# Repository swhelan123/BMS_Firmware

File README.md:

# BMS Firmware

STM32F303VC-based Battery Management System — firmware, desktop tool, and complete
pre-hardware validation stack.

> **No hardware has been flashed yet.**  
> All workflows below run entirely in simulation unless noted otherwise.  
> See [First-Flash Warning](#first-flash-warning) before connecting real hardware.

---

## Quick Start

```bash
# 1. Clone and enter the repo
git clone <repo-url>
cd BMS_Firmware

# 2. Install dev environment (creates .venv, checks toolchain)
./scripts/setup_dev_env.sh

# 3. Run the full validation suite (no hardware needed)
./scripts/validate_all.sh

# 4. Run the interactive CLI demo against the fake target
./scripts/demo_local.sh

# 5. Launch the desktop GUI with the fake target
./scripts/run_gui.sh --fake --mode healthy
```

---

## Project Structure

```
BMS_Firmware/
├── firmware/               STM32F303VC application firmware (C11)
│   ├── src/
│   │   ├── bms/            Core BMS logic (config, faults, balance, measurements)
│   │   ├── drivers/        LTC6812 isoSPI driver, ISL28022 I2C power monitor
│   │   └── board/          STM32 BSP (SPI, UART, outputs, clock, flash)
│   ├── include/            Public headers
│   └── cmake/              Toolchain file + CMakeLists.txt
├── bootloader/             STM32 bootloader (sector 0, 32 KB)
│   ├── src/                bl_validate.c, bl_jump.c, bl_update.c
│   └── include/
├── tool/                   Python desktop tool (CLI + GUI)
│   ├── src/
│   │   ├── core/           AppState, TargetModel, PollingLoop, ConnectionManager
│   │   ├── protocol/       Framing, CRC, BmsProtocolClient, packet_defs
│   │   ├── config/         BmsConfig schema, validator
│   │   ├── update/         Package builder/parser, BootloaderUpdater, ST-Link wrapper
│   │   ├── fake_target/    Full BMS simulator — 12 modes, TCP or in-process
│   │   ├── cli/            bmsctl.py — thin CLI over the shared backend
│   │   ├── gui/            PyQt6 desktop app (9 tabs)
│   │   └── connection/     DeviceState, DeviceMode, CapabilitiesState
│   ├── tests/              ~330 pytest tests (no hardware required)
│   └── requirements.txt    pyserial, PyYAML, pytest, PyQt6
├── tests/                  C unit tests (Unity framework)
│   ├── unit/               test_pec15.c, test_balance.c, test_openwire.c, …
│   ├── mock_bsp/           Mock SPI/UART/outputs/clock/flash
│   └── vendor/unity/
├── scripts/
│   ├── setup_dev_env.sh        One-command dev environment setup
│   ├── validate_all.sh         One-command full validation
│   ├── demo_local.sh           Full stack demo (fake target, CLI, optional GUI)
│   ├── run_gui.sh              Launch GUI (with optional fake target)
│   ├── bmsctl.sh               CLI wrapper (activates .venv)
│   ├── build_firmware.sh       STM32 firmware build
│   ├── flash_stlink.sh         Dry-run and real flash via ST-Link (--execute required)
│   ├── first_flash_dry_run.sh  Pre-hardware readiness check (no flash)
│   └── package_release.sh      Create dist/ release bundle
├── protocol/               Protocol specification documents
├── docs/                   Design documents (hardware contract, safety model, etc.)
└── build_firmware/         CMake build output (gitignored)
```

---

## Setup

```bash
./scripts/setup_dev_env.sh
```

Creates `.venv`, installs `tool/requirements.txt`, and checks for:

| Tool | Required for | Install |
|------|-------------|---------|
| Python 3.11+ | Everything | https://python.org |
| arm-none-eabi-gcc | Firmware build | brew install --cask gcc-arm-embedded |
| cmake | Firmware build | brew install cmake |
| ninja | Firmware build | brew install ninja |
| clang | C unit tests | included with Xcode CLT |
| STM32_Programmer_CLI | ST-Link flash (optional) | https://st.com/stm32cubeprog |
| PyQt6 | Desktop GUI | pip install PyQt6 |

---

## Validate Everything

```bash
./scripts/validate_all.sh                   # full suite with firmware build
./scripts/validate_all.sh --no-firmware     # skip STM32 build
```

Runs: tool detection → pytest suite → fake-target self-test → config round-trip →
package + update simulation → firmware build.

Expected output: `33 passed  0 failed  0-5 skipped` (skipped = optional tools absent).

---

## Run Tests

### Python tests (~330)
```bash
python3 -m pytest tool/tests/ -q
```

### C unit tests (181 across 14 suites)
```bash
bash build_tests/run_tests.sh
```

Covers: PEC-15, measurements decode, protocol CRC, config validate/masks, outputs,
flash layout, bootloader validate, bootloader protocol state machine, faults, cell
balancing, open-wire detection.

---

## Build Firmware

```bash
export PATH="/Applications/ArmGNUToolchain/15.2.rel1/arm-none-eabi/bin:$PATH"
./scripts/build_firmware.sh           # release build
./scripts/build_firmware.sh debug     # debug build
```

Artifacts in `build_firmware/`:

| File | Description |
|------|-------------|
| `firmware.bin` | Raw binary, flash at 0x08008000 |
| `firmware.hex` | Intel HEX, flash at 0x08008000 |
| `bms_firmware.elf` | ELF with debug symbols |
| `firmware.map` | Linker map (section sizes, symbols) |

---

## CLI Tool

```bash
./scripts/bmsctl.sh --help
```

Activates `.venv` automatically.

```bash
# Start fake target in one terminal
./scripts/bmsctl.sh fake-target run --mode healthy

# In another terminal
./scripts/bmsctl.sh connect
./scripts/bmsctl.sh values
./scripts/bmsctl.sh cells -v
./scripts/bmsctl.sh temps
./scripts/bmsctl.sh faults --json
./scripts/bmsctl.sh diagnostics
./scripts/bmsctl.sh openwire run

# Config
./scripts/bmsctl.sh config export-default --out default.bin
./scripts/bmsctl.sh config validate default.bin
./scripts/bmsctl.sh config export-json default.bin
./scripts/bmsctl.sh config apply-ram default.bin

# Package + update
./scripts/bmsctl.sh package build firmware.bin fw.pkg --version 1.0.0
./scripts/bmsctl.sh package validate fw.pkg
./scripts/bmsctl.sh update simulate fw.pkg    # test protocol update flow
./scripts/bmsctl.sh update dry-run fw.pkg     # print steps without running
```

---

## Desktop GUI

```bash
./scripts/run_gui.sh --fake                          # healthy mode
./scripts/run_gui.sh --fake --mode openwire_detected # test open-wire tab
./scripts/run_gui.sh --fake --mode cell_uv           # test undervoltage fault
./scripts/run_gui.sh --fake --mode bootloader        # test update simulation
```

**Tabs:**
| Tab | Description |
|-----|-------------|
| Connection | TCP (fake target) or serial port; device capabilities |
| Bring-Up | Diagnostics counters, GPIO snapshot, chain probes, one-shot measurements, open-wire, balance disable-all |
| Dashboard | Pack voltage, current, state, uptime, polling controls |
| Cells | 75-cell voltage table; measure-once; invalid cells highlighted |
| Temperatures | 75-sensor table; measure-once; invalid sensors highlighted |
| Faults | Active + latched bitmaps; named fault list; clear latched |
| Config | Read/load/save/validate/apply-RAM; export default |
| Firmware Flash | Package inspect/validate; protocol update simulation; ST-Link gate |
| Logs | Event + packet logs |

---

## Fake Target

Simulates the full BMS protocol stack. Available modes:

| Mode | Description |
|------|-------------|
| `healthy` | 75 cells at 3700 mV, 25°C, no faults |
| `safe_invalid` | Zero cells, all temps INVALID, no faults |
| `cell_uv` | cell[0]=2400 mV, FAULT_CELL_UV active |
| `cell_ov` | cell[0]=4300 mV, FAULT_CELL_OV active |
| `temp_invalid` | All temps INVALID, FAULT_TEMP_READ_INVALID |
| `vpack_invalid` | FAULT_VPACK_INVALID active |
| `isospi_fault` | FAULT_ISOSPI_CELL active |
| `config_error` | FAULT_CONFIG_INVALID active |
| `precharge_fault` | FAULT_PRECHARGE_TIMEOUT active |
| `bootloader` | Responds as FIRMWARE_TYPE_BOOTLOADER |
| `openwire_detected` | Open-wire scan returns cell[0] flagged |
| `openwire_pec_fail` | Open-wire scan returns PEC error status |

Self-test (all modes):
```bash
./scripts/bmsctl.sh fake-target self-test
```

---

## Full Demo

```bash
./scripts/demo_local.sh             # CLI demo: connect, measure, config, package
./scripts/demo_local.sh --gui       # same + launch GUI at end
```

---

## First-Flash Preparation

> **No hardware has been flashed yet.** The firmware has been validated in simulation only.
> Read the documents listed below before connecting any hardware.

```bash
# 1. Validate the full software stack (no hardware required)
./scripts/validate_all.sh --no-firmware

# 2. Build firmware (requires arm-none-eabi-gcc)
export PATH="/Applications/ArmGNUToolchain/15.2.rel1/arm-none-eabi/bin:$PATH"
./scripts/build_firmware.sh

# 3. Run the first-flash readiness check (dry-run only, no real flash)
./scripts/first_flash_dry_run.sh

# 4. Read before connecting hardware (in order):
#    docs/bench_safety_checklist.md
#    docs/first_flash_guide.md
#    docs/uart_smoke_test.md
#    docs/01_hardware_contract.md  (especially §16 hardware validation questions)
```

Flash command (after safety checklist is complete):

```bash
# Dry-run first — prints exact command, does not flash
./scripts/flash_stlink.sh --app build_firmware/firmware.bin

# Real flash — requires --execute
./scripts/flash_stlink.sh --app build_firmware/firmware.bin --execute
```

First CLI session after flash:

```bash
PORT=/dev/tty.usbserial-XXXX   # find with: ls /dev/tty.usbserial-*
./scripts/bmsctl.sh connect    --serial $PORT
./scripts/bmsctl.sh diagnostics --serial $PORT
./scripts/bmsctl.sh diag gpio   --serial $PORT
./scripts/bmsctl.sh diag outputs --serial $PORT
```

### First-Flash Documents

| Document | Read when |
|----------|-----------|
| `docs/bench_safety_checklist.md` | Before applying power to the board |
| `docs/first_flash_guide.md` | Full first-flash procedure with pass/fail checklist |
| `docs/uart_smoke_test.md` | Diagnosing serial / protocol connection issues |
| `docs/01_hardware_contract.md` | Pin table, isoSPI topology, open hardware questions |
| `docs/02_safety_model.md` | Permission output semantics and safety invariants |

---

## Package Release

```bash
./scripts/package_release.sh
```

Creates `dist/bms-v{VERSION}/` containing firmware artifacts, Python tool source,
scripts (including `flash_stlink.sh` and `first_flash_dry_run.sh`), docs (including all
first-flash guides), and auto-generated release notes and manifest. No `.venv`,
`__pycache__`, or build caches are included.

---

## What Is Simulated (no hardware needed)

- All 12 fake target modes including fault injection, openwire, bootloader
- Full BMS protocol (framing, CRC, all packet types)
- Firmware update flow: enter-bootloader → begin → chunks → finalize
- Config read/write/validate/apply-RAM
- Cell balancing logic (C unit tests with mock SPI)
- Open-wire detection algorithm (C unit tests with mock SPI)
- Fault bit mapping and masking (C unit tests)
- Package build/parse/validate (Python tests)
- GUI polling, state display, all page interactions
- ST-Link dry-run (generates command without executing)

---

## What Remains Hardware-Dependent

| Item | Status |
|------|--------|
| UART/serial communication with real target | Not tested |
| isoSPI chain bring-up (LTC6812) | Not tested |
| ISL28022 I2C power monitor | Not tested |
| ADC calibration (Vpack, Vbat, Ibat) | Not tested |
| GPIO output states (MasterOK, Discharge, Charge, ChargerSafety) | Not tested |
| Precharge timing | Not tested |
| CAN bus | Not tested |
| Power-latch / power-button | Not tested |
| Thermal runaway under real cell conditions | Not tested |
| Actual flash/erase timing on STM32 | Not tested |
| Bootloader PEC verification on real SPI | Not tested |

---

## First-Flash Warning

> **Read this before connecting any hardware.**

1. The firmware has **not been tested on hardware**. Flash into a bench setup
   with no high-voltage pack attached.
2. `board_outputs_init_safe()` deasserts all permission outputs on startup.
   Verify this physically before attaching any contactor or interlock circuit.
3. Review `docs/01_hardware_contract.md` (pin table) and
   `docs/02_safety_model.md` (safety boundary) before first power-on.
4. Do not enable cell balancing until voltage measurements have been verified
   against a known-good reference.
5. Do not enable charging/discharging permission outputs until all fault
   thresholds have been reviewed and the config has been validated.
6. Use `./scripts/bmsctl.sh diagnostics` on first connect to verify PEC/I2C
   error counters are zero before trusting any measurement.
7. Run `./scripts/bmsctl.sh openwire run` before enabling balance to confirm
   all cell connections are intact.

---

## Design Documents

| Document | Content |
|----------|---------|
| `docs/00_system_purpose.md` | Purpose, safety boundary, what BMS does/doesn't do |
| `docs/01_hardware_contract.md` | Pin table, signal directions, notes |
| `docs/02_safety_model.md` | Fault taxonomy, permission outputs, invariants |
| `docs/03_firmware_architecture.md` | Module structure, state machine, polling loop |
| `docs/04_protocol_contract.md` | Packet format, all packet IDs, error codes |
| `docs/05_config_schema.md` | All config fields, types, ranges, defaults |
| `docs/06_flash_and_bootloader.md` | Flash layout, bootloader update flow |
| `docs/07_desktop_tool_design.md` | Tool architecture, GUI tabs, fake target strategy |
| `docs/08_validation_plan.md` | Test strategy, hardware bring-up checklist |

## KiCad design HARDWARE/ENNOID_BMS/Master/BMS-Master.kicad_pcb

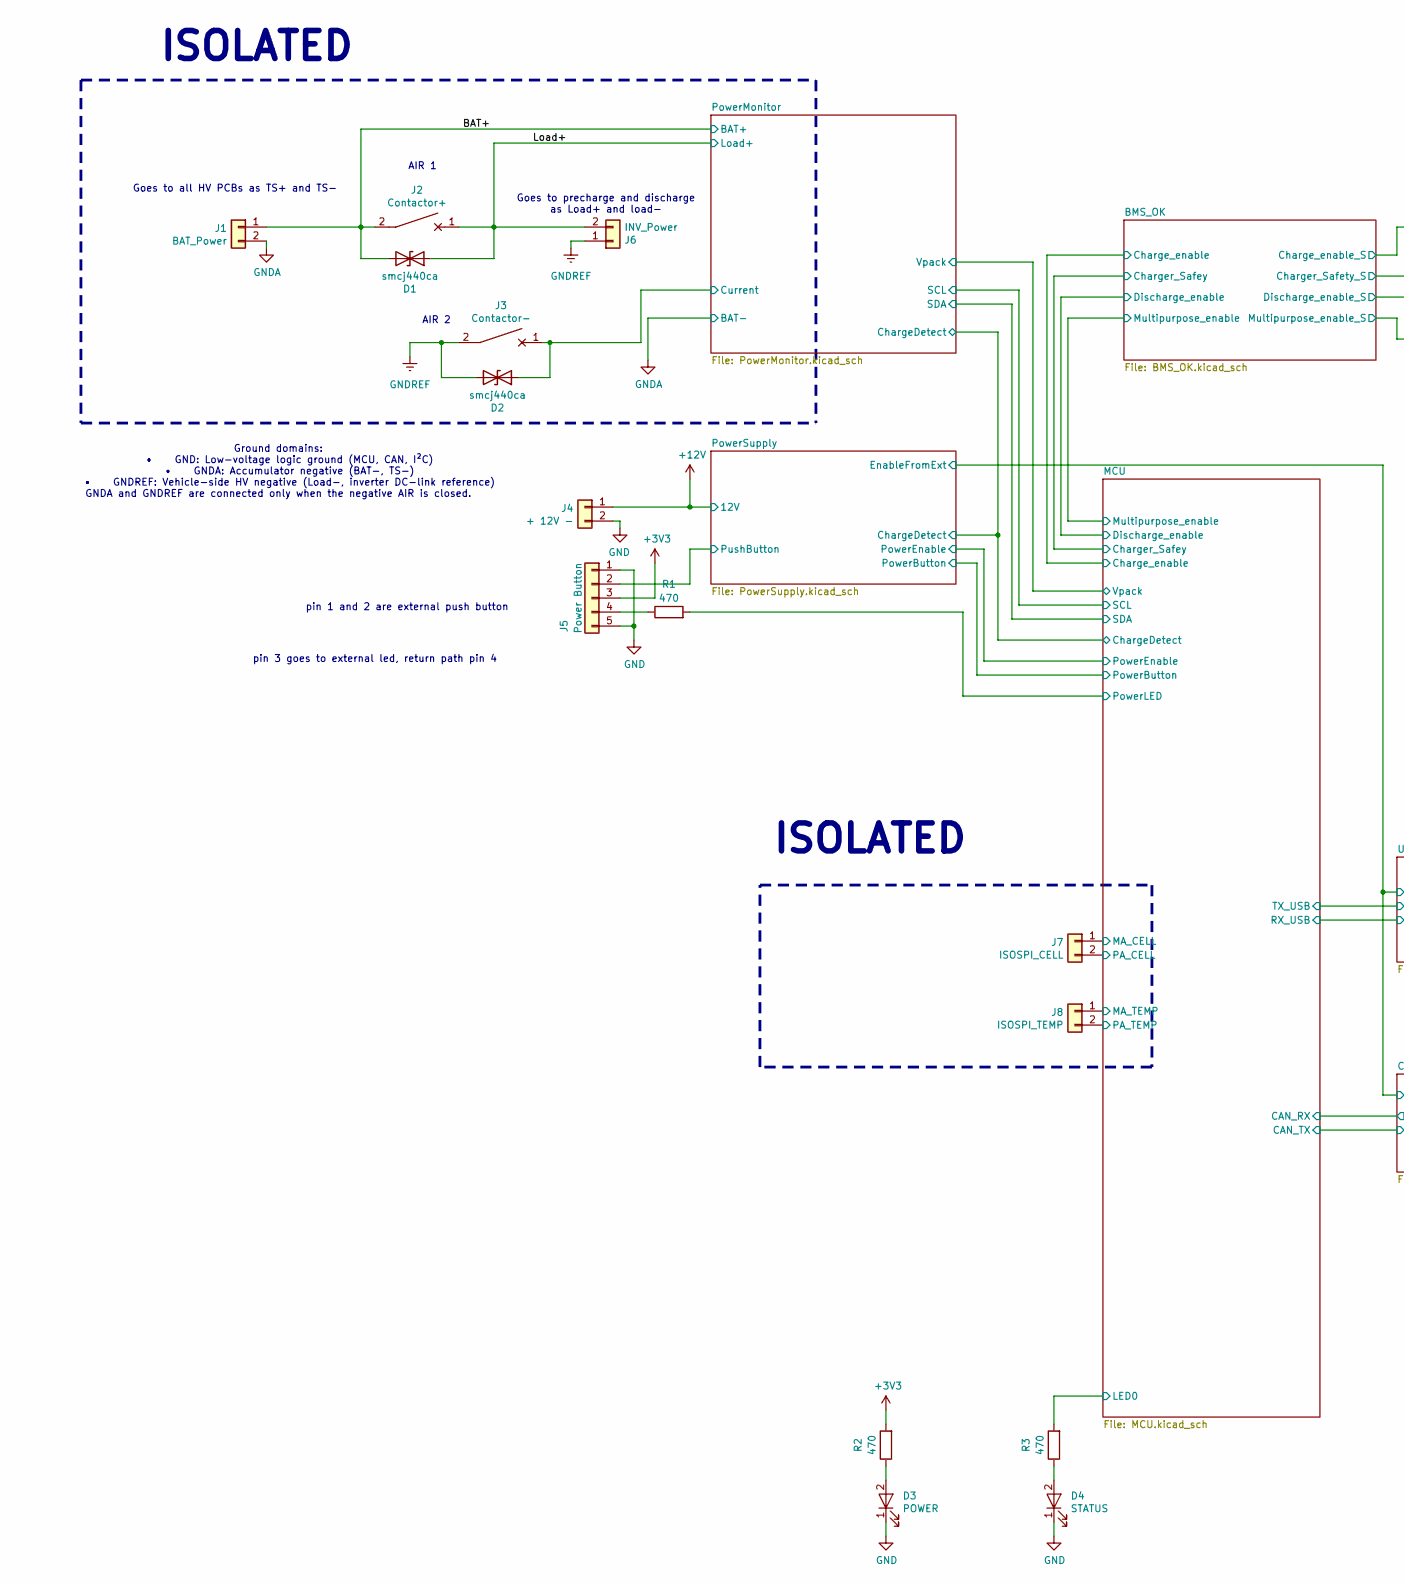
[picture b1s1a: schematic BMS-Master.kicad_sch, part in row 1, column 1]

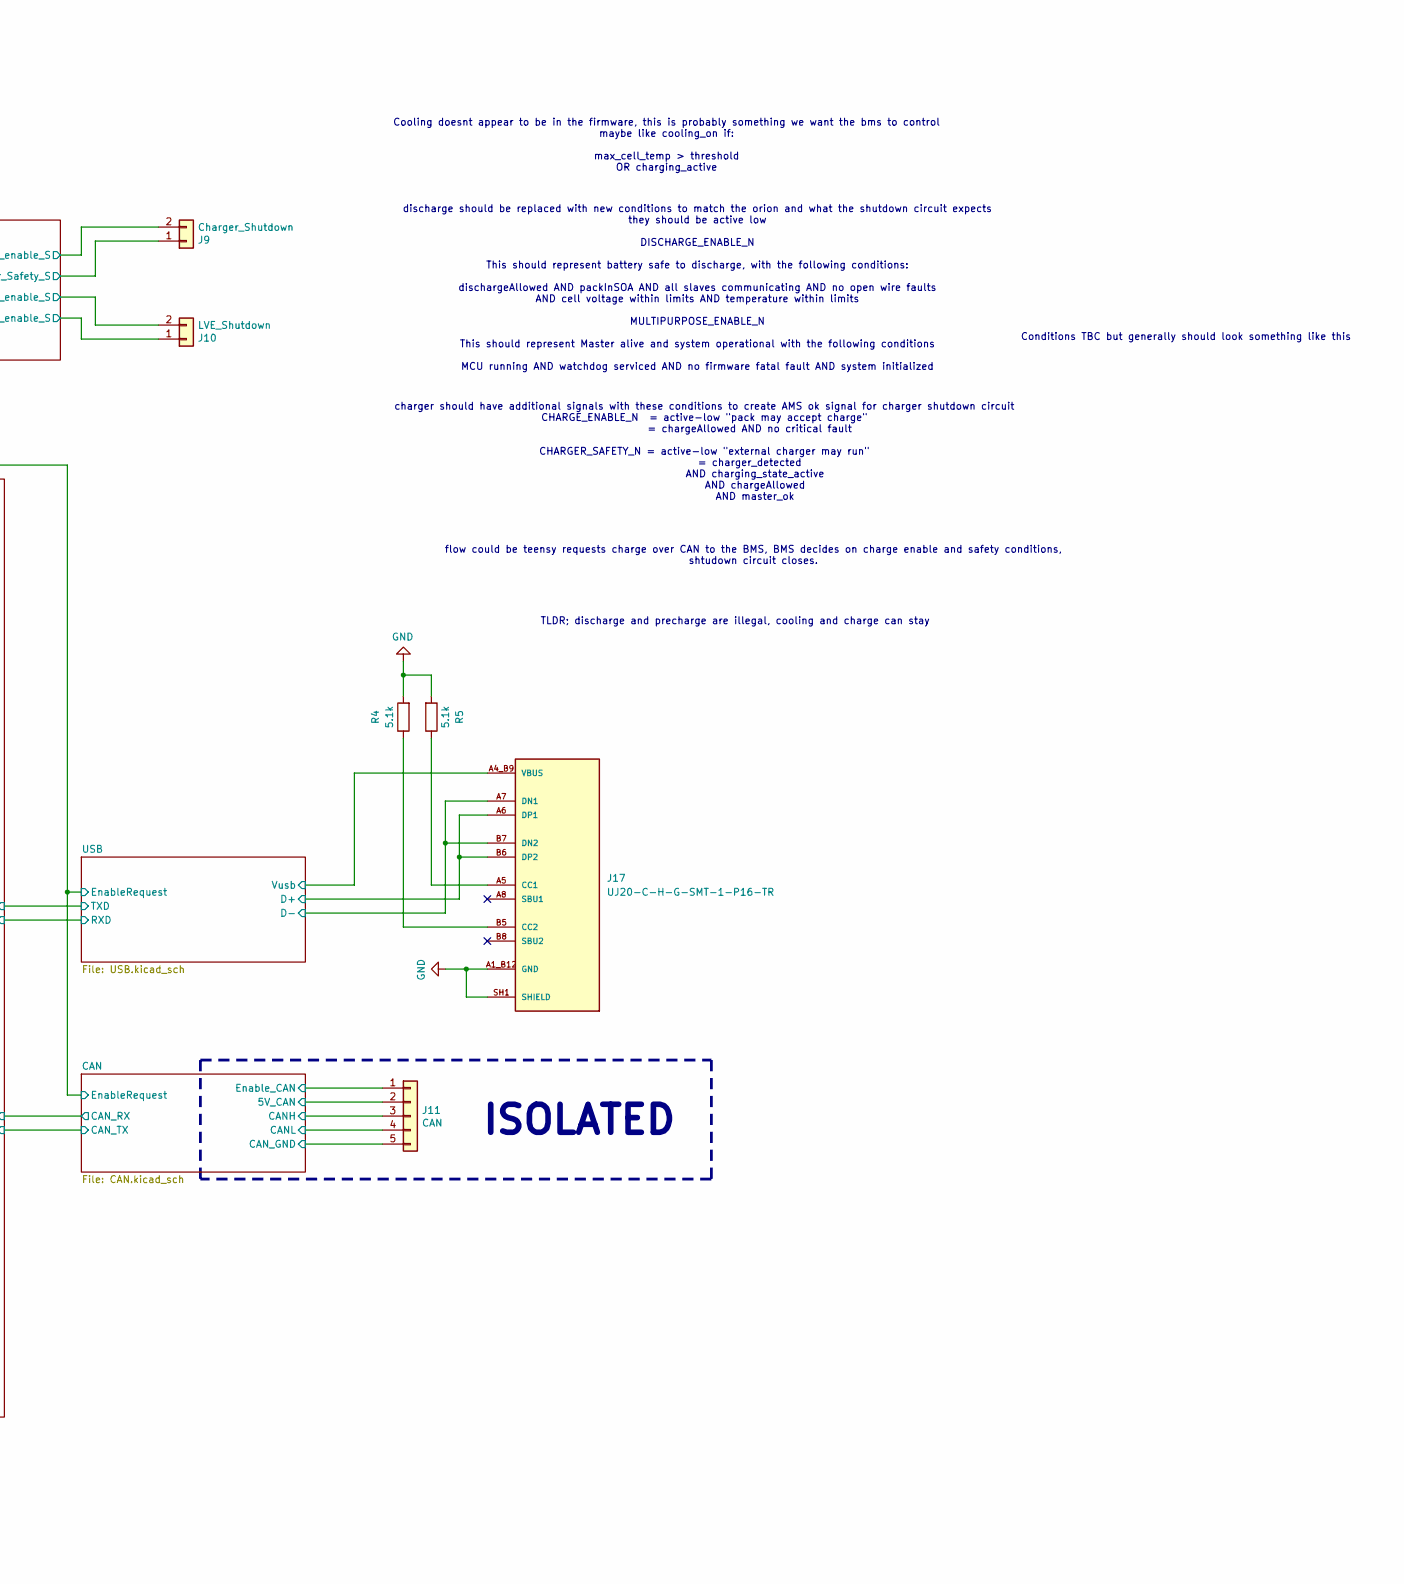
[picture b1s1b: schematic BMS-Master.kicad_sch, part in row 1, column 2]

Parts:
D1, D2: smcj440ca; D_SMC; MPN smcj440ca
D3: POWER; LED_0603_1608Metric; MPN SML-D12P8WT86C
D4: STATUS; LED_0603_1608Metric; MPN SML-D12P8WT86C
J1: BAT_Power; Phoenix_1x2_1729128; MPN 1729128
J2: Contactor+; EVC500; MPN N/A
J3: Contactor-; EVC500; MPN N/A
J4: + 12V -; JST_XH_B2B-XH-A_1x02_P2.50mm_Vertical; MPN B2B-XH-A
J5: Power Button; JST_XH_B5B-XH-A_1x05_P2.50mm_Vertical; MPN B5B-XH-A
J6: INV_Power; Phoenix_1x2_1729128; MPN 1729128
J7: ISOSPI_CELL; JST_XH_B2B-XH-A_1x02_P2.50mm_Vertical; MPN B2B-XH-A
J8: ISOSPI_TEMP; JST_XH_B2B-XH-A_1x02_P2.50mm_Vertical; MPN B2B-XH-A
J9: Charger_Shutdown; JST_XH_B2B-XH-A_1x02_P2.50mm_Vertical; MPN B2B-XH-A
J10: LVE_Shutdown; JST_XH_B2B-XH-A_1x02_P2.50mm_Vertical; MPN B2B-XH-A
J11: CAN; JST_XH_B5B-XH-A_1x05_P2.50mm_Vertical; MPN B5B-XH-A
J17: UJ20-C-H-G-SMT-1-P16-TR; SAMESKY_UJ20-C-H-G-SMT-1-P16-TR; MPN UJ20-C-H-G-SMT-1-P16-TR
R1, R2, R3: 470; R_0603_1608Metric; MPN RC0603JR-07470RL
R4, R5: 5.1k; R_0603_1608Metric; MPN RC0603JR-075K1L

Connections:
+3V3: J5.3, R2.2; also elsewhere on the board
+12V: J4.1; also elsewhere on the board
/BAT+: D1.2 (A2), J1.1, J2.2; also elsewhere on the board
/BMS_OK/Charge_enable_S: J9.2; also elsewhere on the board
/BMS_OK/Charger_Safety_S: J9.1; also elsewhere on the board
/BMS_OK/Discharge_enable_S: J10.2; also elsewhere on the board
/BMS_OK/Multipurpose_enable_S: J10.1; also elsewhere on the board
/CAN/5V_CAN: J11.2; also elsewhere on the board
/CAN/CANH: J11.3; also elsewhere on the board
/CAN/CANL: J11.4; also elsewhere on the board
/CAN/CAN_GND: J11.5; also elsewhere on the board
/CAN/Enable_CAN: J11.1; also elsewhere on the board
/Load+: D1.1 (A1), J2.1, J6.2; also elsewhere on the board
/MCU/LED0: R3.2; also elsewhere on the board
/MCU/MA_CELL: J7.1; also elsewhere on the board
/MCU/MA_TEMP: J8.1; also elsewhere on the board
/MCU/PA_CELL: J7.2; also elsewhere on the board
/MCU/PA_TEMP: J8.2; also elsewhere on the board
/MCU/PowerLED: R1.2; also elsewhere on the board
/PowerMonitor/Current: D2.1 (A1), J3.1; also elsewhere on the board
/PowerSupply/PushButton: J5.2; also elsewhere on the board
/USB/D+: J17.A6 (DP1), J17.B6 (DP2); also elsewhere on the board
/USB/D-: J17.A7 (DN1), J17.B7 (DN2); also elsewhere on the board
/USB/Vusb: J17.A4_B9 (VBUS), J17.B4_A9 (VBUS); also elsewhere on the board
GND: D3.1 (K), D4.1 (K), J4.2, J5.1, J5.5, J17.A1_B12 (GND), J17.B1_A12 (GND), J17.SH1 (SHIELD), J17.SH2 (SHIELD), J17.SH3 (SHIELD), J17.SH4 (SHIELD), R4.2, R5.2; also elsewhere on the board
GNDA: J1.2; also elsewhere on the board
GNDREF: D2.2 (A2), J3.2, J6.1; also elsewhere on the board
unnamed: D3.2 (A), R2.1
unnamed: D4.2 (A), R3.1
unnamed: J5.4, R1.1
unnamed: J17.A5 (CC1), R5.1
unnamed: J17.B5 (CC2), R4.1

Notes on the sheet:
Ground domains: • GND: Low-voltage logic ground (MCU, CAN, I²C) • GNDA: Accumulator negative (BAT−, TS−) • GNDREF: Vehicle-side HV negative (Load−, inverter DC-link reference) GNDA and GNDREF are connected only when the negative AIR is closed.
Goes to all HV PCBs as TS+ and TS-
flow could be teensy requests charge over CAN to the BMS, BMS decides on charge enable and safety conditions, shtudown circuit closes.
Conditions TBC but generally should look something like this
AIR 1
ISOLATED
pin 3 goes to external led, return path pin 4
charger should have additional signals with these conditions to create AMS ok signal for charger shutdown circuit CHARGE_ENABLE_N = active-low "pack may accept charge" = chargeAllowed AND no critical fault CHARGER_SAFETY_N = active-low "external charger may run" = charger_detected AND charging_stat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
AIR 2
Cooling doesnt appear to be in the firmware, this is probably something we want the bms to control maybe like cooling_on if: max_cell_temp > threshold OR charging_active
discharge should be replaced with new conditions to match the orion and what the shutdown circuit expects they should be active low DISCHARGE_ENABLE_N This should represent battery safe to discharge, with the following conditions: dischargeAllowed AND packInSOA AND all slaves communicating AND no o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
Goes to precharge and discharge as Load+ and load-
pin 1 and 2 are external push button
TLDR; discharge and precharge are illegal, cooling and charge can stay

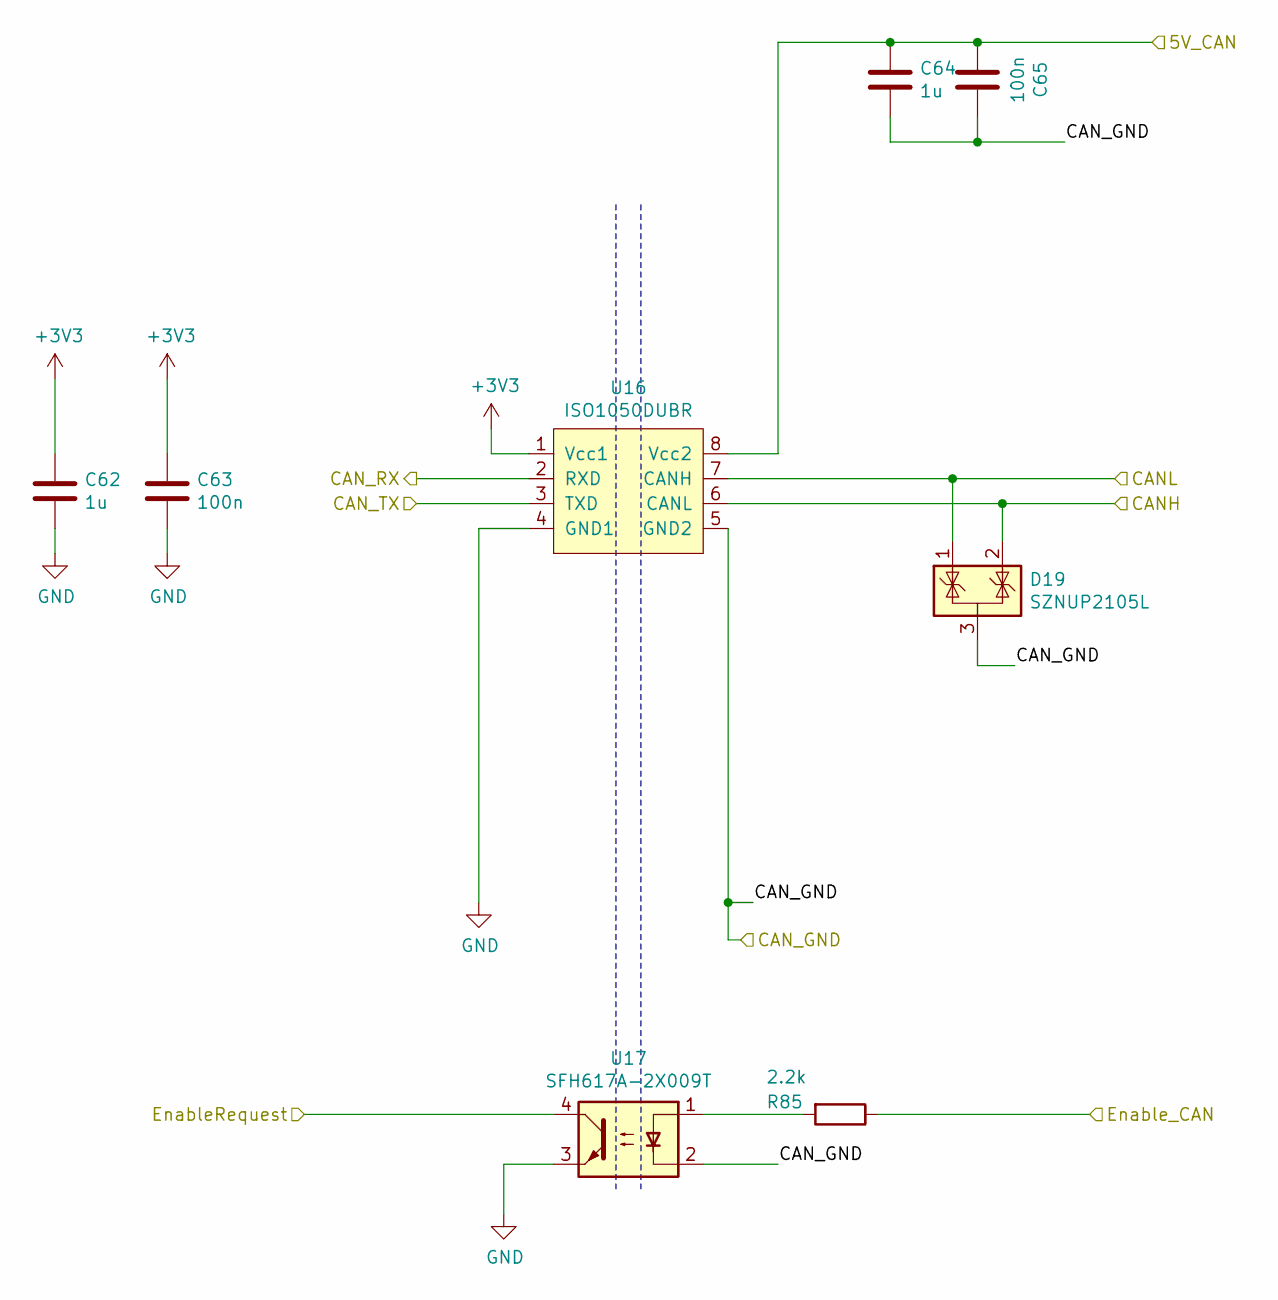
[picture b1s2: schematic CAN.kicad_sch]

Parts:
C62, C64: 1u; C_0603_1608Metric; MPN GRM188R71E105KA12D
C63, C65: 100n; C_0603_1608Metric; MPN GRM188R71E104KA01D
D19: SZNUP2105L; SOT-23; MPN SZNUP2105LT1G
R85: 2.2k; R_0603_1608Metric; MPN RC0603JR-072K2L
U16: ISO1050DUBR; ISO1050; MPN ISO1050DUBR
U17: SFH617A-2X009T; SMDIP-4_W9.53mm_Clearance8mm; MPN SFH617A-2X009T

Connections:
+3V3: C62.1, C63.1, U16.1 (Vcc1); also elsewhere on the board
/CAN/5V_CAN: C64.1, C65.2, U16.8 (Vcc2); also elsewhere on the board
/CAN/CANH: D19.2 (K), U16.6 (CANL); also elsewhere on the board
/CAN/CANL: D19.1 (K), U16.7 (CANH); also elsewhere on the board
/CAN/CAN_GND: C64.2, C65.1, D19.3 (A), U16.5 (GND2), U17.2; also elsewhere on the board
/CAN/CAN_RX: U16.2 (RXD); also elsewhere on the board
/CAN/CAN_TX: U16.3 (TXD); also elsewhere on the board
/CAN/EnableRequest: U17.4; also elsewhere on the board
/CAN/Enable_CAN: R85.1; also elsewhere on the board
GND: C62.2, C63.2, U16.4 (GND1), U17.3; also elsewhere on the board
unnamed: R85.2, U17.1

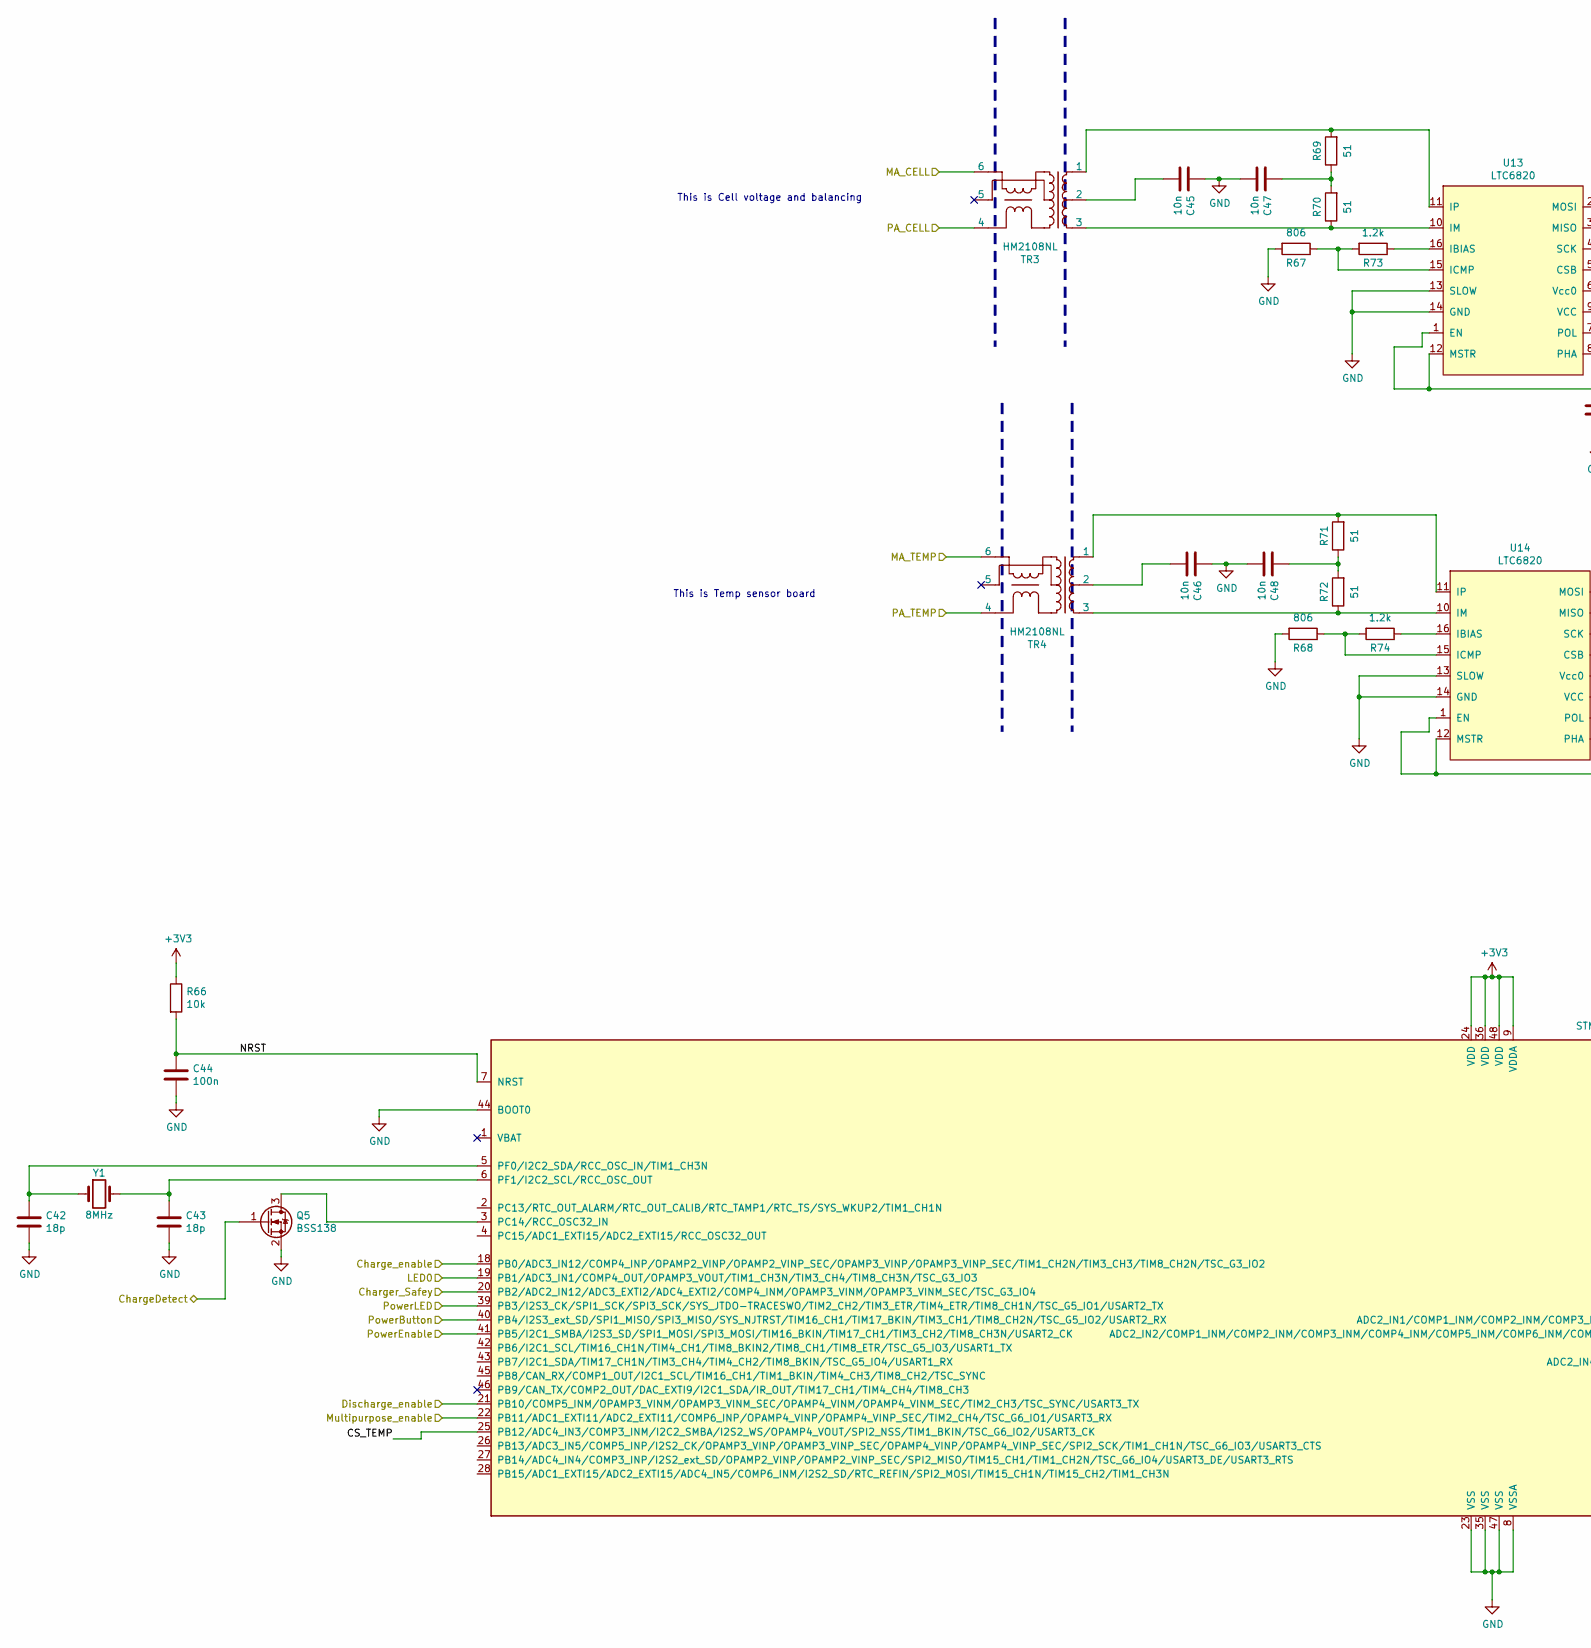
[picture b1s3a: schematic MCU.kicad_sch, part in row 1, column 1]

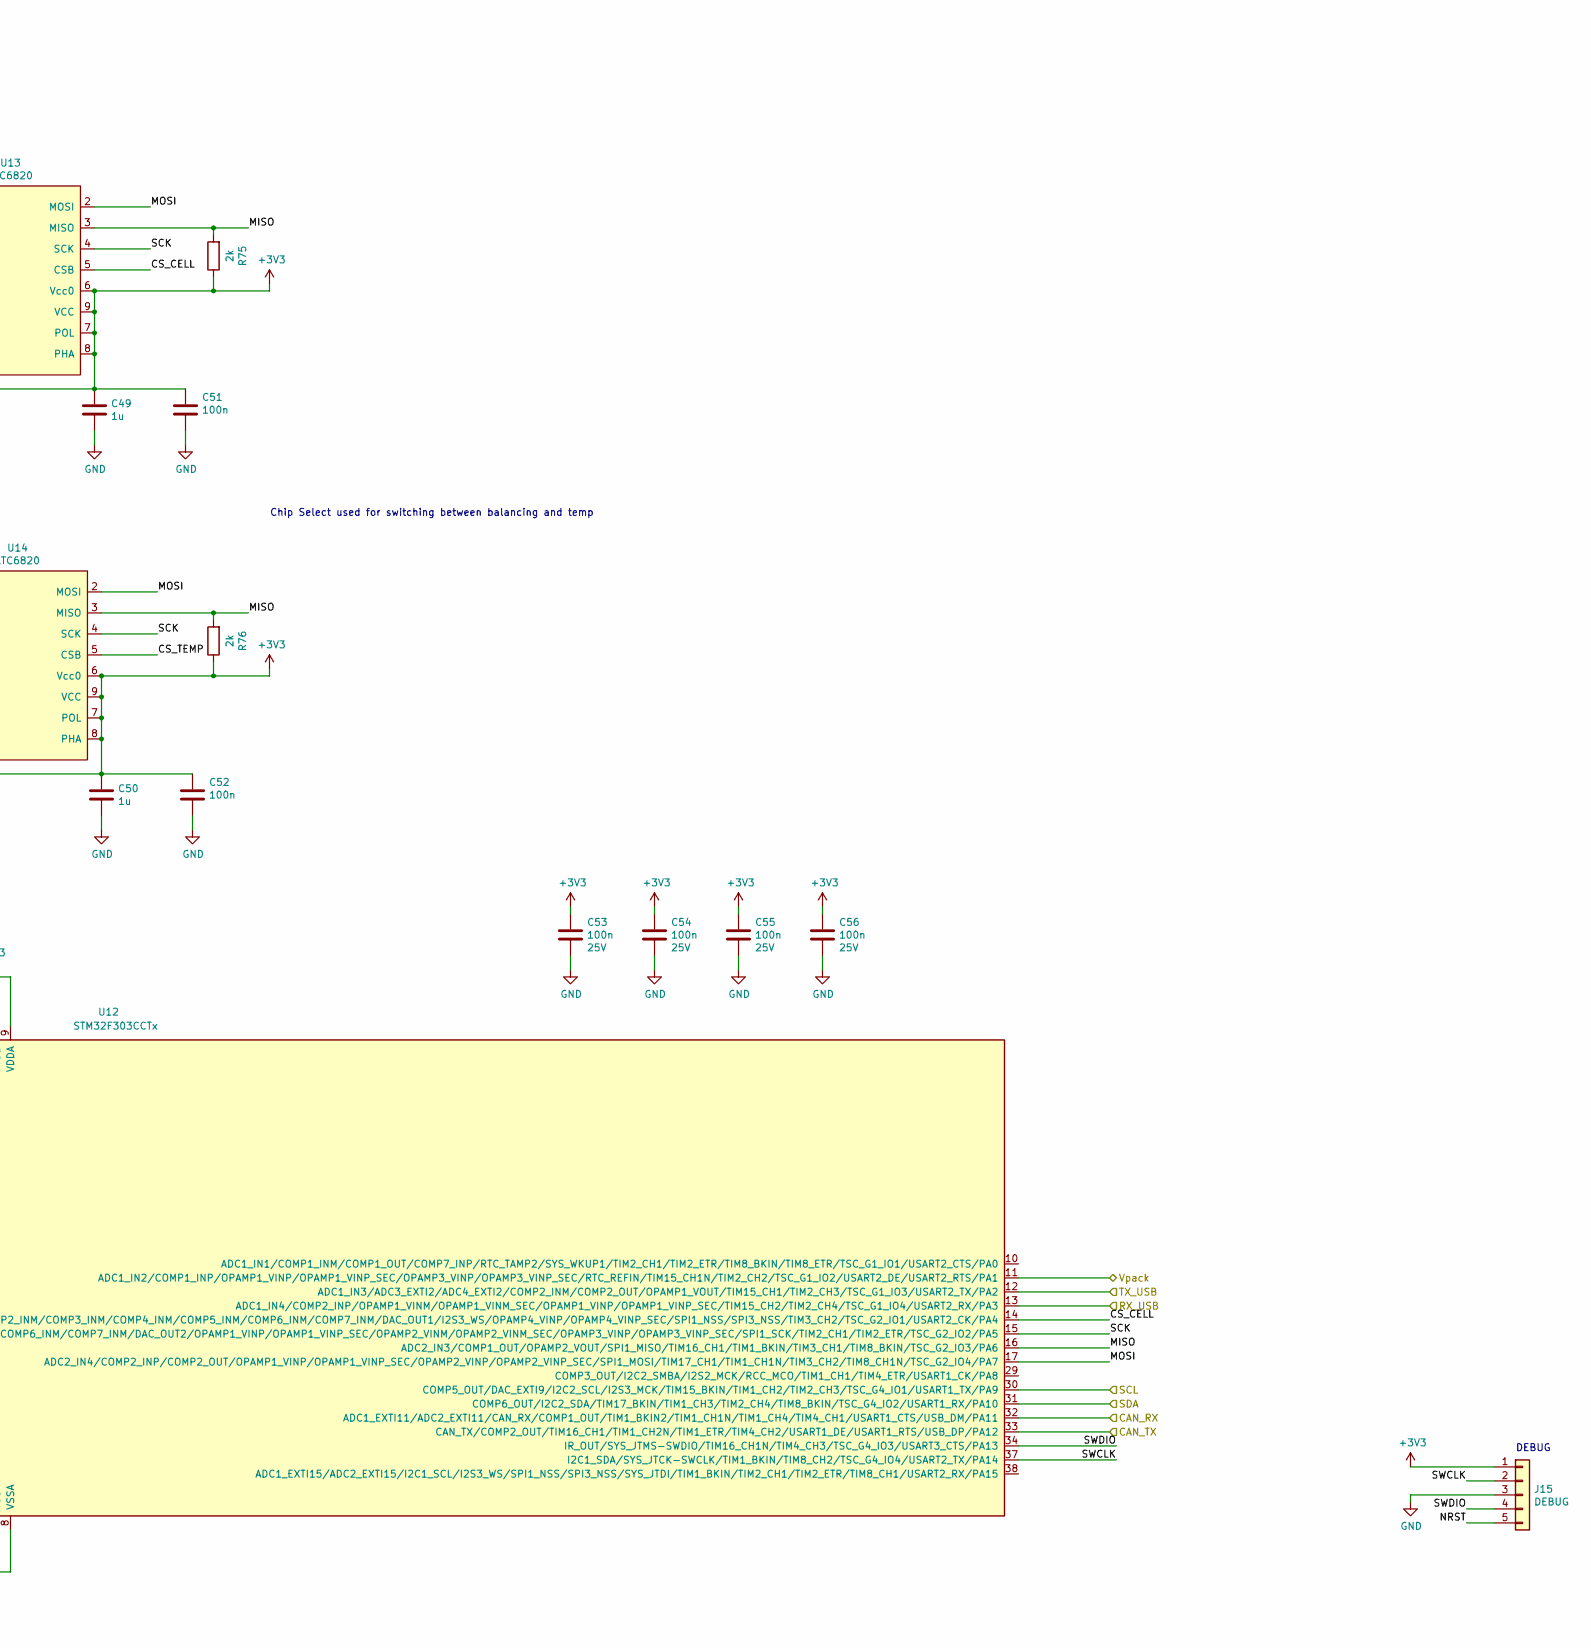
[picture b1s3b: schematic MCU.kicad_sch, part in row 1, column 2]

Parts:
C42, C43: 18p; C_0603_1608Metric; Voltage 50V; MPN GRM1885C1H180JA01D
C44: 100n; C_0603_1608Metric; MPN GRM188R71E104KA01D
C45, C46, C47, C48: 10n; C_0603_1608Metric; MPN 885012206114
C49, C50: 1u; C_0603_1608Metric; MPN GRM188R71E105KA12D
C51, C52, C53, C54, C55, C56: 100n; C_0603_1608Metric; Voltage 25V; MPN GRM188R71E104KA01D
J15: DEBUG; JST_XH_B5B-XH-A_1x05_P2.50mm_Vertical; MPN B5B-XH-A
Q5: BSS138; SOT-23; MPN BSS138
R66: 10k; R_0603_1608Metric; MPN RC0603FR-0710KL
R67, R68: 806; R_0603_1608Metric; MPN RC0603FR-07806RL
R69, R70, R71, R72: 51; R_0603_1608Metric; MPN RC0603JR-0751RL
R73, R74: 1.2k; R_0603_1608Metric; MPN RC0603JR-071K2L
R75, R76: 2k; R_0603_1608Metric; MPN RC0603FR-072KL
TR3, TR4: HM2108NL; MPN HM2108NL
U12: STM32F303CCTx; LQFP-48_7x7mm_P0.5mm; MPN STM32F303CCT6
U13, U14: LTC6820; MSOP-16_3x4.039mm_P0.5mm; MPN LTC6820IMS#PBF
Y1: 8MHz; Crystal_SMD_Abracon_ABM3-2Pin_5.0x3.2mm; MPN ABM3-8.000MHZ-D2Y-T

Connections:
+3V3: C49.2, C50.2, C51.1, C52.1, C53.1, C54.1, C55.1, C56.1, J15.1, R66.1, R75.1, R76.1, U12.9 (VDDA), U12.24 (VDD), U12.36 (VDD), U12.48 (VDD), U13.1 (EN), U13.6 (Vcc0), U13.7 (POL), U13.8 (PHA), U13.9 (VCC), U13.12 (MSTR), U14.1 (EN), U14.6 (Vcc0), U14.7 (POL), U14.8 (PHA), U14.9 (VCC), U14.12 (MSTR); also elsewhere on the board
/BMS_OK/Charge_enable: U12.18 (PB0/ADC3_IN12/COMP4_INP/OPAMP2_VINP/OPA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); also elsewhere on the board
/BMS_OK/Charger_Safey: U12.20 (PB2/ADC2_IN12/ADC3_EXTI2/ADC4_EXTI2/COM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); also elsewhere on the board
/BMS_OK/Discharge_enable: U12.21 (PB10/COMP5_INM/OPAMP3_VINM/OPAMP3_VINM_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); also elsewhere on the board
/BMS_OK/Multipurpose_enable: U12.22 (PB11/ADC1_EXTI11/ADC2_EXTI11/COMP6_INP/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); also elsewhere on the board
/CAN/CAN_RX: U12.32 (ADC1_EXTI11/ADC2_EXTI11/CAN_RX/COMP1_OU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); also elsewhere on the board
/CAN/CAN_TX: U12.33 (CAN_TX/COMP2_OUT/TIM16_CH1/TIM1_CH2N/TI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); also elsewhere on the board
/MCU/CS_CELL: U12.14 (ADC2_IN1/COMP1_INM/COMP2_INM/COMP3_INM/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), U13.5 (CSB)
/MCU/CS_TEMP: U12.25 (PB12/ADC4_IN3/COMP3_INM/I2C2_SMBA/I2S2_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), U14.5 (CSB)
/MCU/LED0: U12.19 (PB1/ADC3_IN1/COMP4_OUT/OPAMP3_VOUT/TIM1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); also elsewhere on the board
/MCU/MA_CELL: TR3.6; also elsewhere on the board
/MCU/MA_TEMP: TR4.6; also elsewhere on the board
/MCU/MISO: R75.2, R76.2, U12.16 (ADC2_IN3/COMP1_OUT/OPAMP2_VOUT/SPI1_MIS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), U13.3 (MISO), U14.3 (MISO)
/MCU/MOSI: U12.17 (ADC2_IN4/COMP2_INP/COMP2_OUT/OPAMP1_VIN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), U13.2 (MOSI), U14.2 (MOSI)
/MCU/NRST: C44.1, J15.5, R66.2, U12.7 (NRST)
/MCU/PA_CELL: TR3.4; also elsewhere on the board
/MCU/PA_TEMP: TR4.4; also elsewhere on the board
/MCU/PowerButton: U12.40 (PB4/I2S3_ext_SD/SPI1_MISO/SPI3_MISO/SYS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); also elsewhere on the board
/MCU/PowerEnable: U12.41 (PB5/I2C1_SMBA/I2S3_SD/SPI1_MOSI/SPI3_MO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); also elsewhere on the board
/MCU/PowerLED: U12.39 (PB3/I2S3_CK/SPI1_SCK/SPI3_SCK/SYS_JTDO-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); also elsewhere on the board
/MCU/RX_USB: U12.13 (ADC1_IN4/COMP2_INP/OPAMP1_VINM/OPAMP1_V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); also elsewhere on the board
/MCU/SCK: U12.15 (ADC2_IN2/COMP1_INM/COMP2_INM/COMP3_INM/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), U13.4 (SCK), U14.4 (SCK)
/MCU/SCL: U12.30 (COMP5_OUT/DAC_EXTI9/I2C2_SCL/I2S3_MCK/T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); also elsewhere on the board
/MCU/SDA: U12.31 (COMP6_OUT/I2C2_SDA/TIM17_BKIN/TIM1_CH3/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); also elsewhere on the board
/MCU/SWCLK: J15.2, U12.37 (I2C1_SDA/SYS_JTCK-SWCLK/TIM1_BKIN/TIM8_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)
/MCU/SWDIO: J15.4, U12.34 (IR_OUT/SYS_JTMS-SWDIO/TIM16_CH1N/TIM4_C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)
/MCU/TX_USB: U12.12 (ADC1_IN3/ADC3_EXTI2/ADC4_EXTI2/COMP2_IN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); also elsewhere on the board
/MCU/Vpack: U12.11 (ADC1_IN2/COMP1_INP/OPAMP1_VINP/OPAMP1_V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); also elsewhere on the board
/PowerSupply/ChargeDetect: Q5.1 (G); also elsewhere on the board
GND: C42.2, C43.2, C44.2, C45.2, C46.2, C47.1, C48.1, C49.1, C50.1, C51.2, C52.2, C53.2, C54.2, C55.2, C56.2, J15.3, Q5.2 (S), R67.2, R68.2, U12.8 (VSSA), U12.23 (VSS), U12.35 (VSS), U12.44 (BOOT0), U12.47 (VSS), U13.13 (SLOW), U13.14 (GND), U14.13 (SLOW), U14.14 (GND); also elsewhere on the board
unnamed: C45.1, TR3.2
unnamed: C46.1, TR4.2
unnamed: C47.2, R69.1, R70.2
unnamed: C48.2, R71.1, R72.2
unnamed: Q5.3 (D), U12.3 (PC14/RCC_OSC32_IN)
unnamed: C42.1, U12.5 (PF0/I2C2_SDA/RCC_OSC_IN/TIM1_CH3N), Y1.1
unnamed: C43.1, U12.6 (PF1/I2C2_SCL/RCC_OSC_OUT), Y1.2
unnamed: R73.1, U13.16 (IBIAS)
unnamed: R67.1, R73.2, U13.15 (ICMP)
unnamed: R70.1, TR3.3, U13.10 (IM)
unnamed: R69.2, TR3.1, U13.11 (IP)
unnamed: R74.1, U14.16 (IBIAS)
unnamed: R68.1, R74.2, U14.15 (ICMP)
unnamed: R72.1, TR4.3, U14.10 (IM)
unnamed: R71.2, TR4.1, U14.11 (IP)

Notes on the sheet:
This is Temp sensor board
Chip Select used for switching between balancing and temp
This is Cell voltage and balancing
DEBUG
